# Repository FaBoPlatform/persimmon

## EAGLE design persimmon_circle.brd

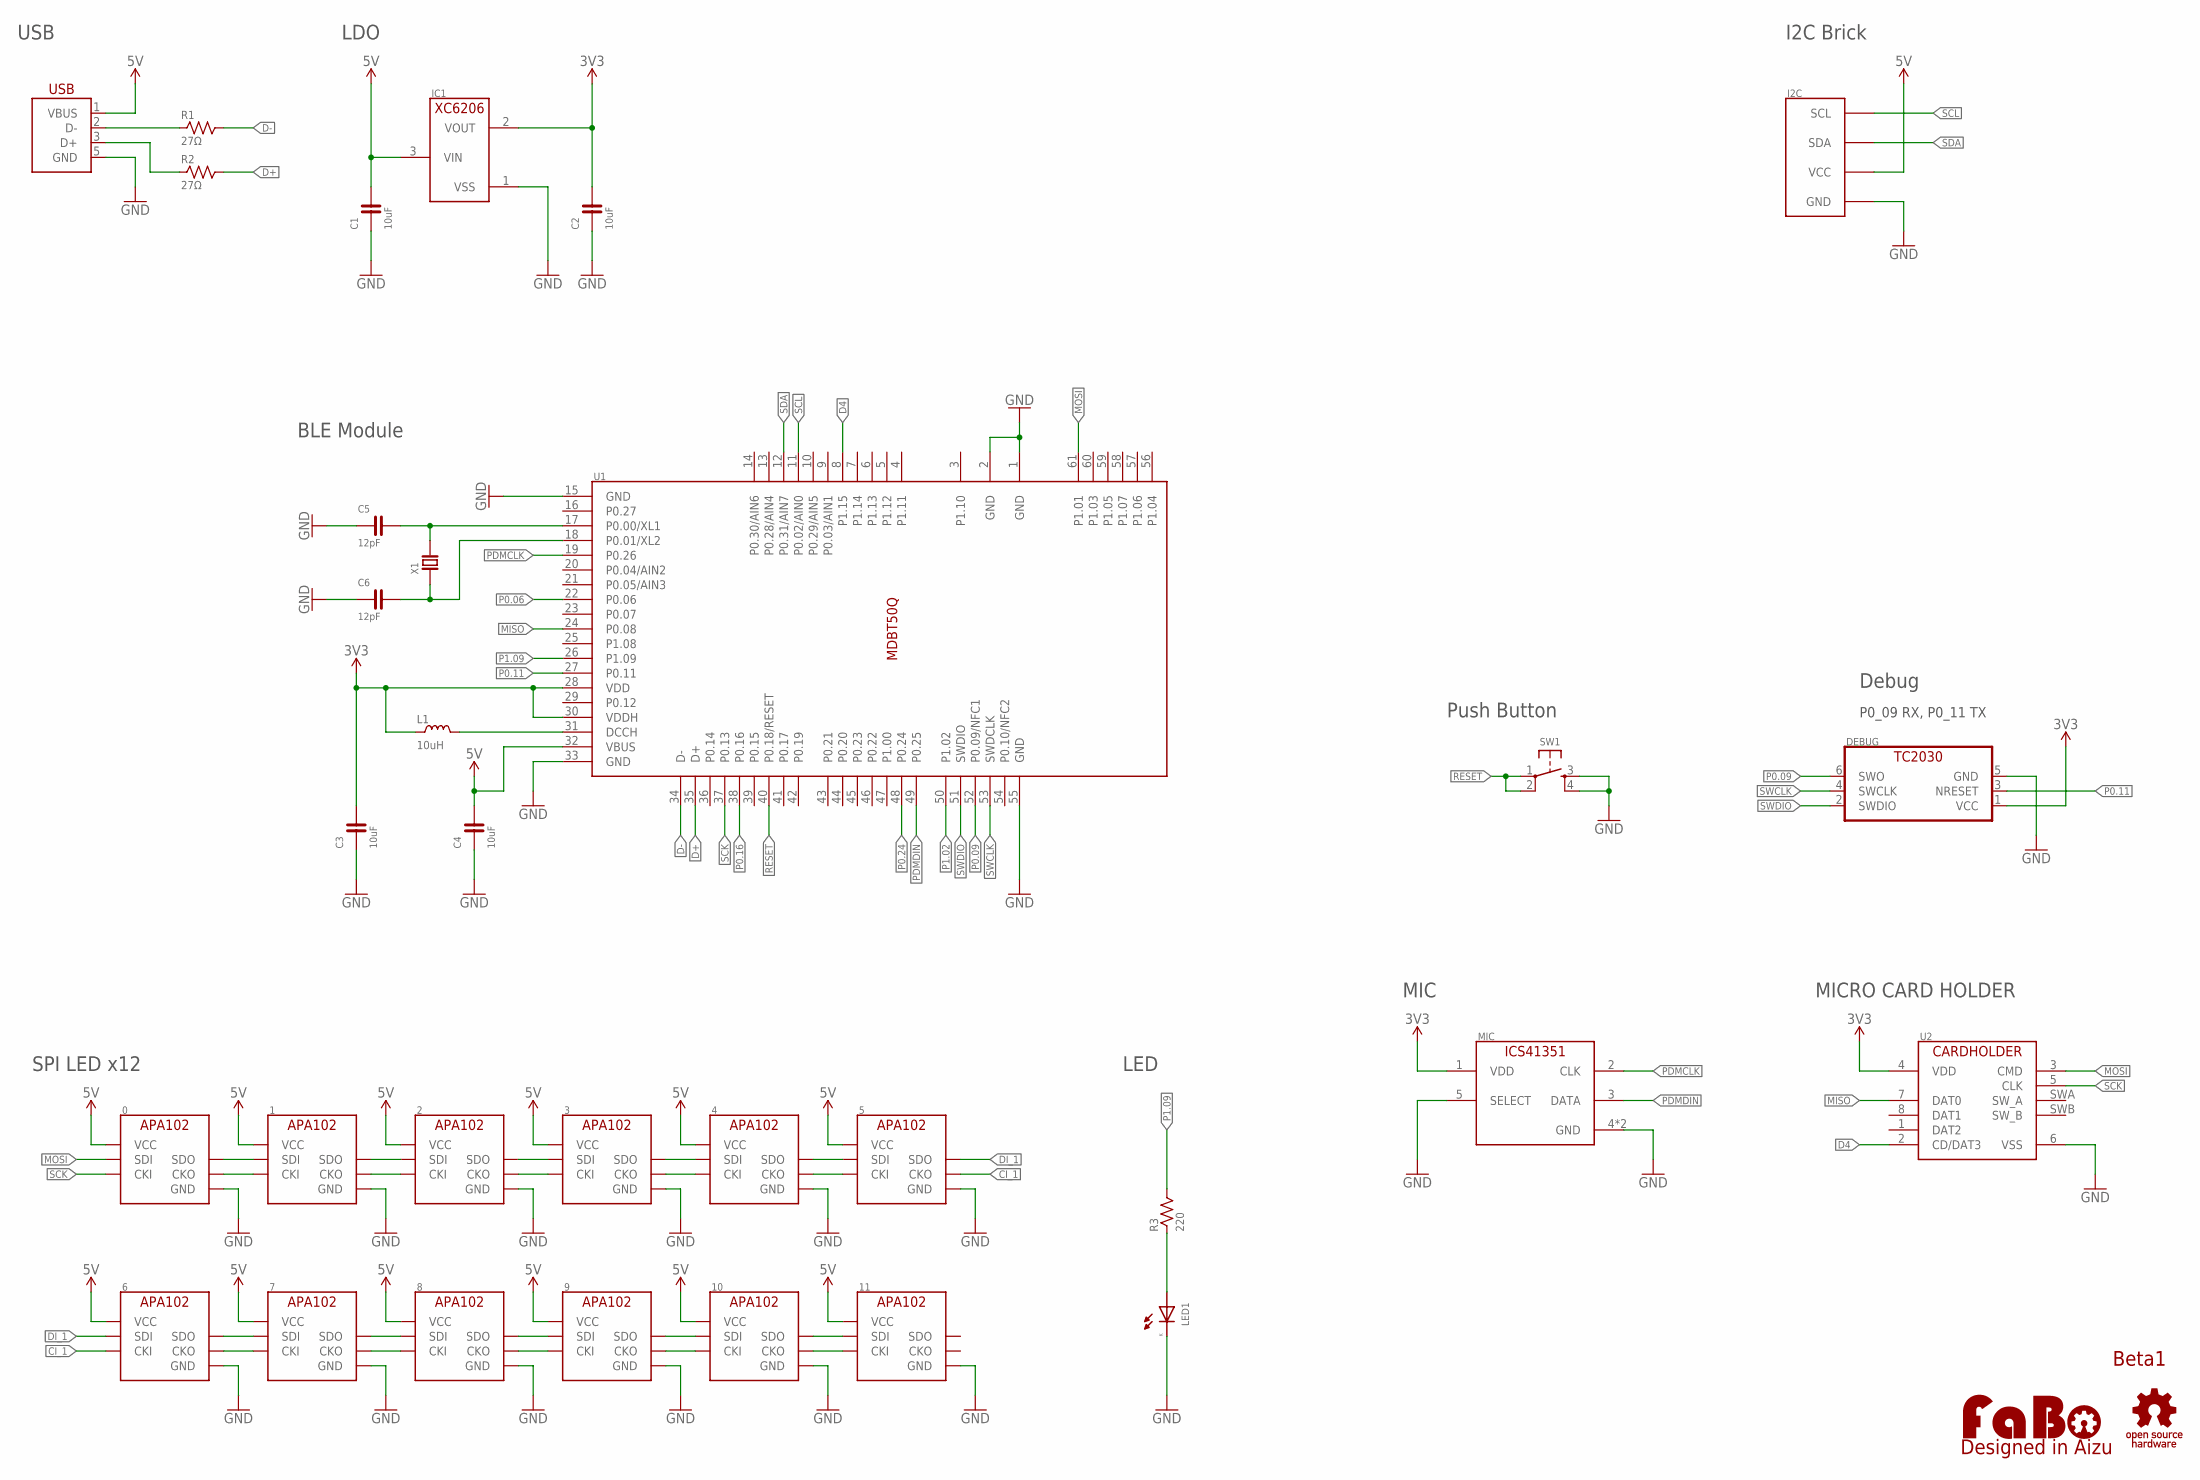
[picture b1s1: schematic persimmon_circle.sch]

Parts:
0, 1, 2, 3, 4, 5, 6, 7, 8, 9, 10, 11: APA102_IPIXEL; APA102_2020
C1, C2, C3, C4: 10uF; 0603
C5, C6: 12pF; 0603
DEBUG: TC2030-IDC-NL
I2C: FABO_BRICK_I2C-B04B-PASK-1; FABO_BRICK_I2C_B04B-PASK-1
IC1: XC6206; SOT-23
L1: 10uH; 0603
LED1: LED-0603; 0603
LOGO1: LOGO_OSHW-M_BOTTOM; LOGO_OSHW_M_BOTTOM
LOGO2: LOGO_FABO-M; LOGO_FABO_M
MIC: TDK-ICS41351; ICS41351
R1, R2: 27Ω; 0603
R3: 220; 0603
SW1: TACT-SWITCH-SMD_KMR2; KMR2
U1: MDBT50
U2: CARDHOLDER_MICRO; DM3AT-SF-PEJM5
USB: USB-ZX62D-B-5PA8; ZX62D-B-5PA8
X1: CRYSTAL-ABS07; ABRACON-ABS07-32.768KHZ

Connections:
3V3: C2.2, C3.2, DEBUG.1 (VCC), IC1.2 (VOUT), L1.1, MIC.1 (VDD), U1.28 (VDD), U1.30 (VDDH), U2.4 (VDD)
5V: 0.VCC, 1.VCC, 2.VCC, 3.VCC, 4.VCC, 5.VCC, 6.VCC, 7.VCC, 8.VCC, 9.VCC, 10.VCC, 11.VCC, C1.2, C4.2, I2C.VCC, IC1.3 (VIN), U1.32 (VBUS), USB.1 (VBUS)
CI0: 0.CKO, 1.CKI
CI1: 1.CKO, 2.CKI
CI2: 2.CKO, 3.CKI
CI3: 3.CKO, 4.CKI
CI4: 4.CKO, 5.CKI
CI6: 6.CKO, 7.CKI
CI7: 7.CKO, 8.CKI
CI8: 8.CKO, 9.CKI
CI9: 9.CKO, 10.CKI
CI10: 10.CKO, 11.CKI
CI_1: 5.CKO, 6.CKI
D4: U1.8 (P1.15), U2.2 (CD/DAT3)
D+: R2.2, U1.35 (D+)
D-: R1.2, U1.34 (D-)
DI0: 0.SDO, 1.SDI
DI1: 1.SDO, 2.SDI
DI2: 2.SDO, 3.SDI
DI3: 3.SDO, 4.SDI
DI4: 4.SDO, 5.SDI
DI6: 6.SDO, 7.SDI
DI7: 7.SDO, 8.SDI
DI8: 8.SDO, 9.SDI
DI9: 9.SDO, 10.SDI
DI10: 10.SDO, 11.SDI
DI_1: 5.SDO, 6.SDI
GND: 0.GND, 1.GND, 2.GND, 3.GND, 4.GND, 5.GND, 6.GND, 7.GND, 8.GND, 9.GND, 10.GND, 11.GND, C1.1, C2.1, C3.1, C4.1, C5.1, C6.1, DEBUG.5 (GND), I2C.GND, IC1.1 (VSS), LED1.CATHODE, MIC.4 (GND), MIC.5 (SELECT), MIC.6 (GND), SW1.3, SW1.4, U1.1 (GND), U1.2 (GND), U1.15 (GND), U1.33 (GND), U1.55 (GND), U2.6 (VSS), USB.5 (GND)
L1: L1.2, U1.31 (DCCH)
LED1: LED1.ANODE, R3.1
MISO: U1.24 (P0.08), U2.7 (DAT0)
MOSI: 0.SDI, U1.61 (P1.01), U2.3 (CMD)
P0.06: U1.22 (P0.06)
P0.09: DEBUG.6 (SWO), U1.52 (P0.09/NFC1)
P0.11: DEBUG.3 (NRESET), U1.27 (P0.11)
P0.16: U1.38 (P0.16)
P0.24: U1.48 (P0.24)
P1.02: U1.50 (P1.02)
P1.09: R3.2, U1.26 (P1.09)
PDMCLK: MIC.2 (CLK), U1.19 (P0.26)
PDMDIN: MIC.3 (DATA), U1.49 (P0.25)
RESET: SW1.1, SW1.2, U1.40 (P0.18/RESET)
SCK: 0.CKI, U1.37 (P0.13), U2.5 (CLK)
SCL: I2C.SCL, U1.11 (P0.02/AIN0)
SDA: I2C.SDA, U1.12 (P0.31/AIN7)
SWCLK: DEBUG.4 (SWCLK), U1.53 (SWDCLK)
SWDIO: DEBUG.2 (SWDIO), U1.51 (SWDIO)
USB_DM: R1.1, USB.2 (D-)
USB_DP: R2.1, USB.3 (D+)
X1: C5.2, U1.17 (P0.00/XL1), X1.P$2
X2: C6.2, U1.18 (P0.01/XL2), X1.P$1

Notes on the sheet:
Push Button
BLE Module
Debug
P0_09 RX, P0_11 TX
MIC
Beta1
USB
SPI LED x12
MICRO CARD HOLDER
I2C Brick
LED
LDO

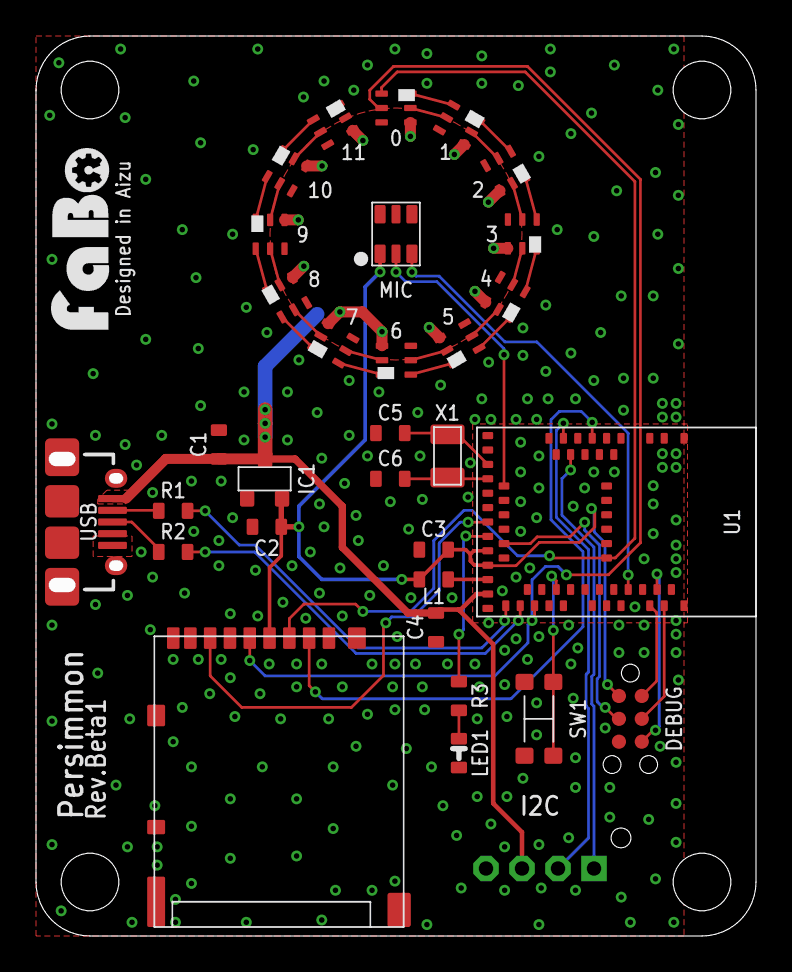
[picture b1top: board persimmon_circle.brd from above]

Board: 2 copper layers, 39.2 x 49.2 mm, 34 parts (0 on the bottom side), 47 nets.

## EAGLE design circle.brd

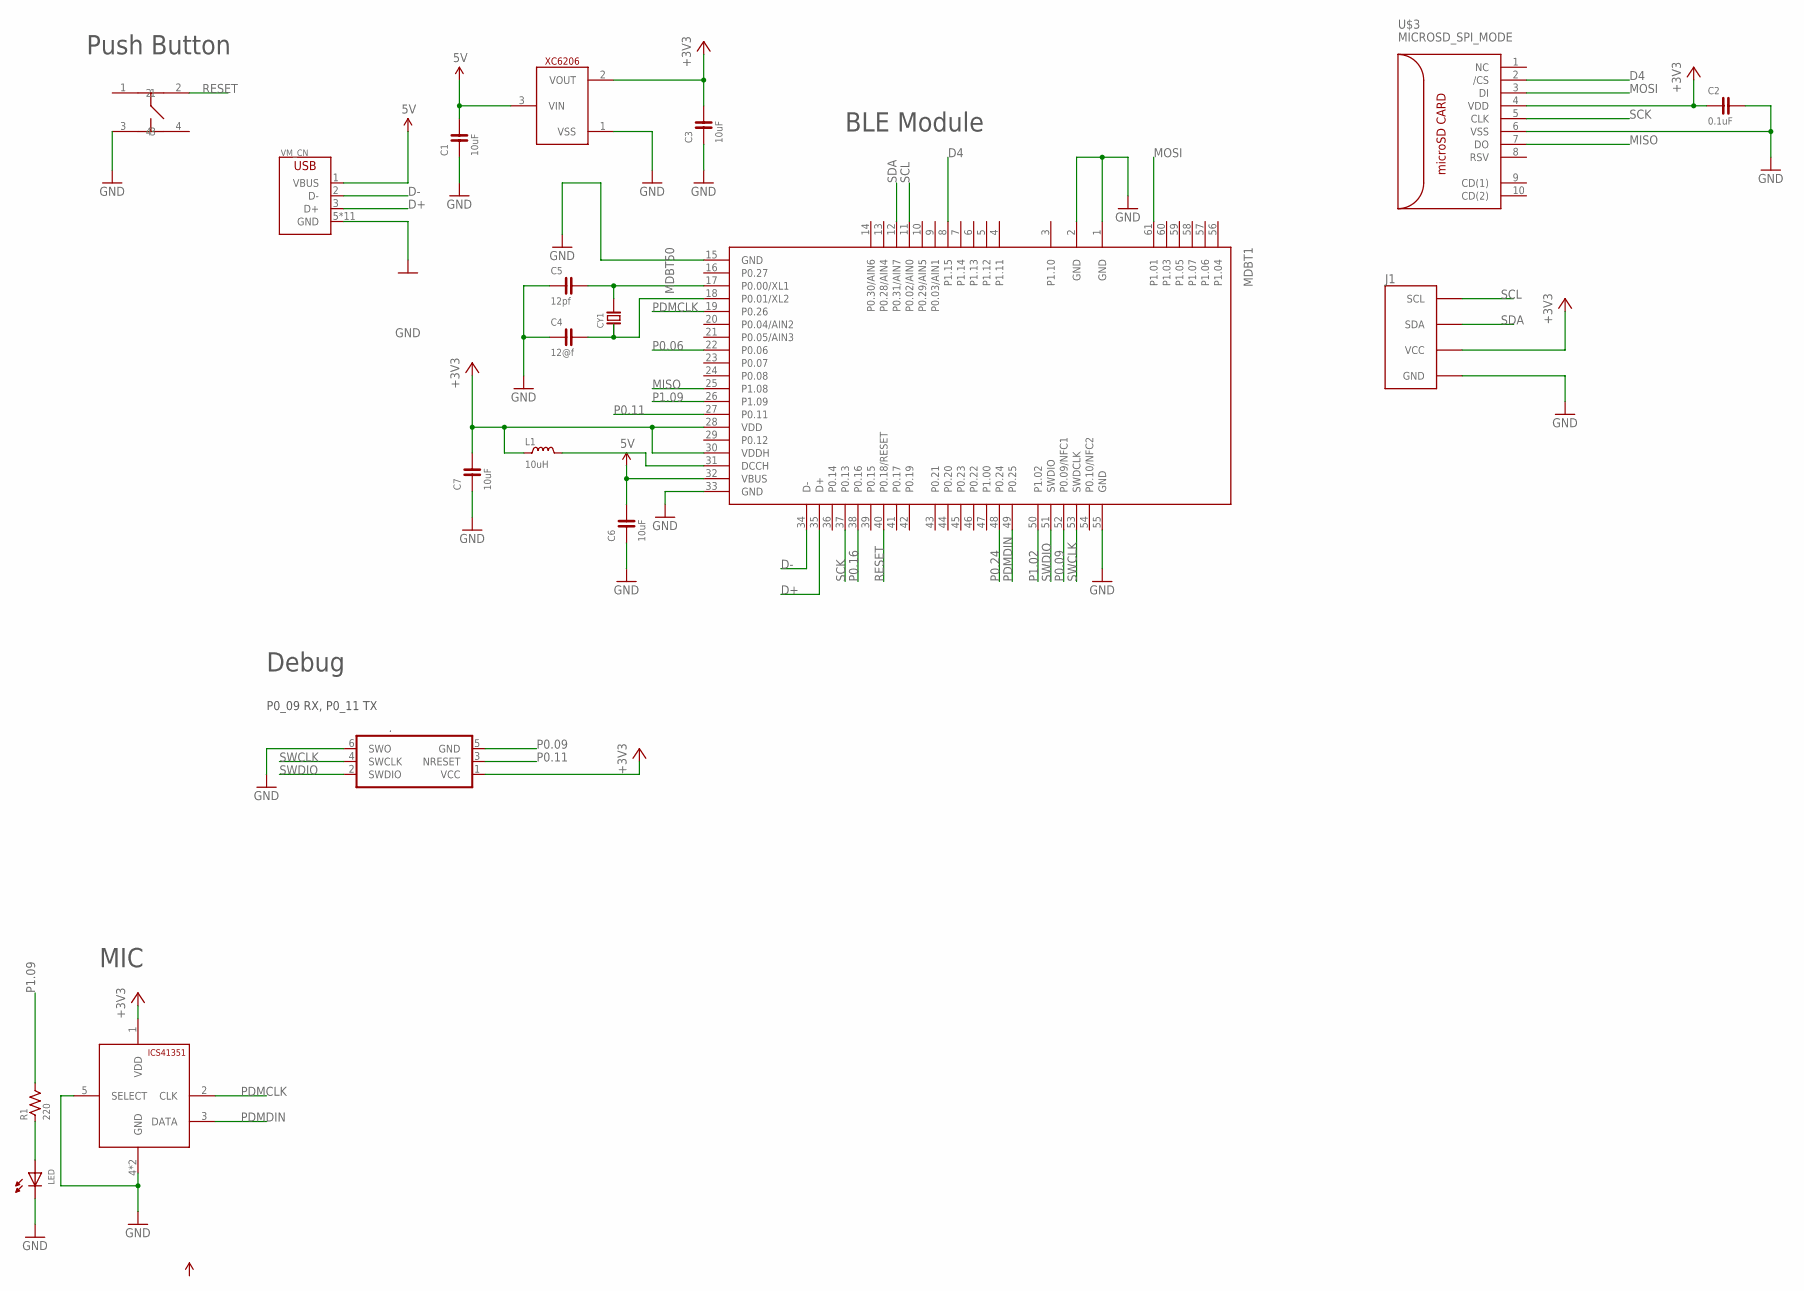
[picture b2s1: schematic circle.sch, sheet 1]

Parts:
.: TC2030-IDC-NL
C1, C3, C6, C7: 10uF; 0603
C2: 0.1uF; 0603
C4: 12@f; 0603
C5: 12pf; 0603
CY1: CRYSTAL-ABS07; ABRACON-ABS07-32.768KHZ
IC1: XC6206; SOT-23
J1: FABO_BRICK_I2C-B04B-PASK-1; FABO_BRICK_I2C_B04B-PASK-1
L1: 10uH; 0603
LED: LED-0603; 0603
MDBT1: MDBT50
MIC1: TDK-ICS41351; ICS41351
R1: 220; 0603
U$3: MICROSD_SPI_MODE; MICRO_SD_CONNECTOR
U$5: SWICTH-4P(KMR2); SWITCH-4P(KMR2)
VM_CN: USB-ZX62D; ZX62D-B-5PA8

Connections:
5V: C1.2, C6.2, IC1.3 (VIN), MDBT1.32 (VBUS), VM_CN.1 (VBUS)
+3V3: ..1 (VCC), C2.1, C3.2, C7.2, IC1.2 (VOUT), J1.VCC, L1.1, MDBT1.28 (VDD), MDBT1.30 (VDDH), MIC1.1 (VDD), U$3.4 (VDD)
D4: MDBT1.8 (P1.15), U$3.2 (/CS)
D+: MDBT1.35 (D+), VM_CN.3 (D+)
D-: MDBT1.34 (D-), VM_CN.2 (D-)
GND: ..6 (SWO), C1.1, C2.2, C3.1, C4.1, C5.1, C6.1, C7.1, IC1.1 (VSS), J1.GND, LED.CATHODE, MDBT1.1 (GND), MDBT1.2 (GND), MDBT1.15 (GND), MDBT1.33 (GND), MDBT1.55 (GND), MIC1.4 (GND), MIC1.5 (SELECT), MIC1.6 (GND), U$3.6 (VSS), U$5.3, VM_CN.5 (GND), VM_CN.B1 (GND), VM_CN.B2 (GND), VM_CN.B3 (GND), VM_CN.B4 (GND), VM_CN.T1 (GND), VM_CN.T2 (GND), VM_CN.T3 (GND), VM_CN.T4 (GND), VM_CN.T5 (GND), VM_CN.T6 (GND); also elsewhere on the board
MISO: MDBT1.25 (P1.08), U$3.7 (DO)
MOSI: MDBT1.61 (P1.01), U$3.3 (DI); also elsewhere on the board
unnamed: L1.2, MDBT1.31 (DCCH)
unnamed: LED.ANODE, R1.1
unnamed: C5.2, CY1.P$2, MDBT1.17 (P0.00/XL1)
unnamed: C4.2, CY1.P$1, MDBT1.18 (P0.01/XL2)
P0.06: MDBT1.22 (P0.06)
P0.09: ..5 (GND), MDBT1.52 (P0.09/NFC1)
P0.11: ..3 (NRESET), MDBT1.27 (P0.11)
P0.16: MDBT1.38 (P0.16)
P0.24: MDBT1.48 (P0.24)
P1.02: MDBT1.50 (P1.02)
P1.09: MDBT1.26 (P1.09), R1.2
PDMCLK: MDBT1.19 (P0.26), MIC1.2 (CLK)
PDMDIN: MDBT1.49 (P0.25), MIC1.3 (DATA)
RESET: MDBT1.40 (P0.18/RESET), U$5.2
SCK: MDBT1.37 (P0.13), U$3.5 (CLK); also elsewhere on the board
SCL: J1.SCL, MDBT1.11 (P0.02/AIN0)
SDA: J1.SDA, MDBT1.12 (P0.31/AIN7)
SWCLK: ..4 (SWCLK), MDBT1.53 (SWDCLK)
SWDIO: ..2 (SWDIO), MDBT1.51 (SWDIO)

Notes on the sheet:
Push Button
BLE Module
Debug
P0_09 RX, P0_11 TX
MIC

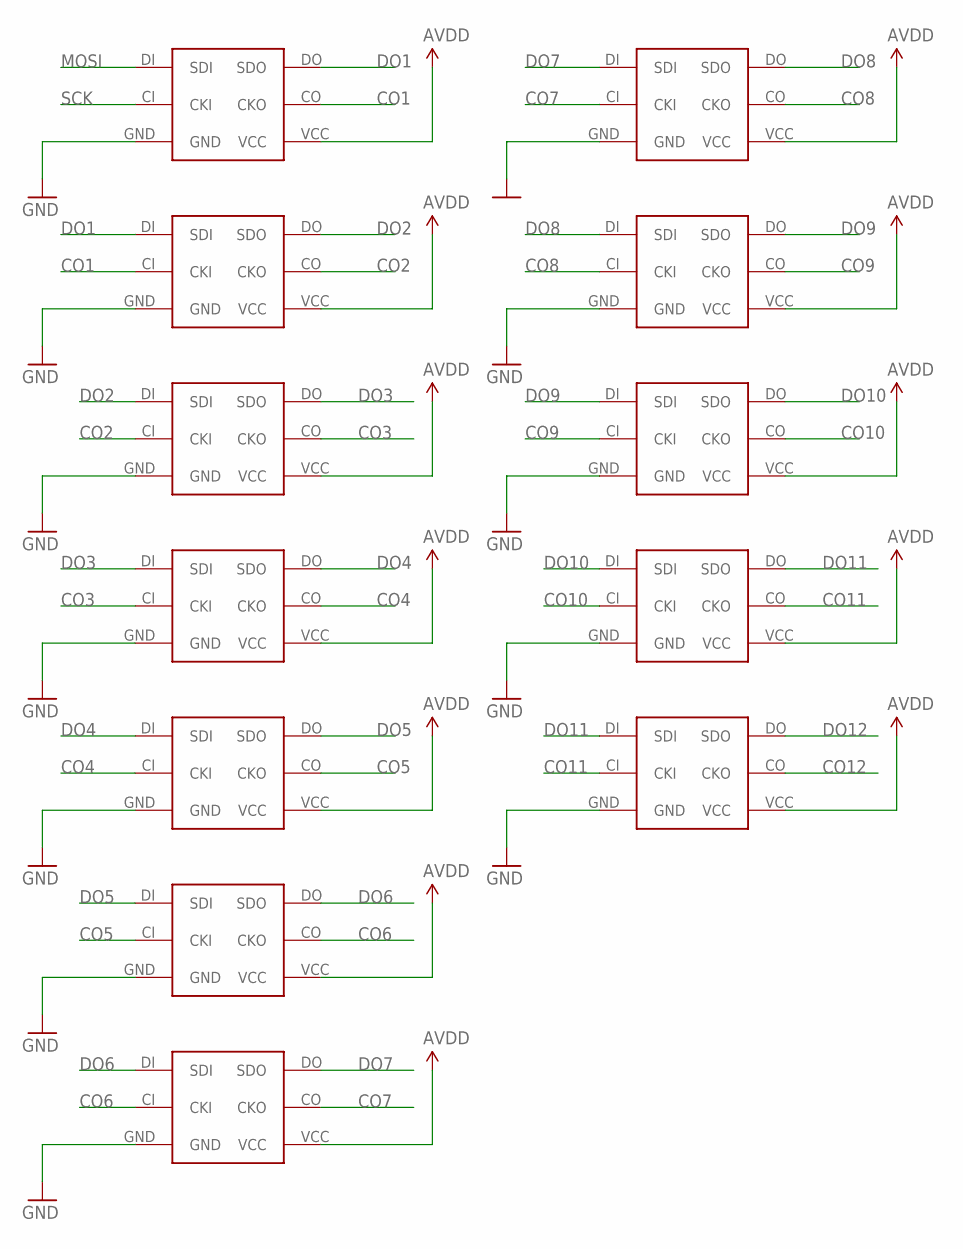
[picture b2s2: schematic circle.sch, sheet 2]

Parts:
0, 1, 2, 3, 4, 5, 6, 7, 8, 9, 10, 11: APA102_IPIXEL; APA102(IPIXEL)

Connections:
AVDD: 0.VCC, 1.VCC, 2.VCC, 3.VCC, 4.VCC, 5.VCC, 6.VCC, 7.VCC, 8.VCC, 9.VCC, 10.VCC, 11.VCC
CO1: 0.CO (CKO), 1.CI (CKI)
CO2: 1.CO (CKO), 2.CI (CKI)
CO3: 2.CO (CKO), 3.CI (CKI)
CO4: 3.CO (CKO), 4.CI (CKI)
CO5: 4.CO (CKO), 5.CI (CKI)
CO6: 5.CO (CKO), 6.CI (CKI)
CO7: 6.CO (CKO), 7.CI (CKI)
CO8: 7.CO (CKO), 8.CI (CKI)
CO9: 8.CO (CKO), 9.CI (CKI)
CO10: 9.CO (CKO), 10.CI (CKI)
CO11: 10.CO (CKO), 11.CI (CKI)
CO12: 11.CO (CKO)
DO1: 0.DO (SDO), 1.DI (SDI)
DO2: 1.DO (SDO), 2.DI (SDI)
DO3: 2.DO (SDO), 3.DI (SDI)
DO4: 3.DO (SDO), 4.DI (SDI)
DO5: 4.DO (SDO), 5.DI (SDI)
DO6: 5.DO (SDO), 6.DI (SDI)
DO7: 6.DO (SDO), 7.DI (SDI)
DO8: 7.DO (SDO), 8.DI (SDI)
DO9: 8.DO (SDO), 9.DI (SDI)
DO10: 9.DO (SDO), 10.DI (SDI)
DO11: 10.DO (SDO), 11.DI (SDI)
DO12: 11.DO (SDO)
GND: 0.GND, 1.GND, 2.GND, 3.GND, 4.GND, 5.GND, 6.GND, 7.GND, 8.GND, 9.GND, 10.GND, 11.GND; also elsewhere on the board
MOSI: 0.DI (SDI); also elsewhere on the board
SCK: 0.CI (CKI); also elsewhere on the board

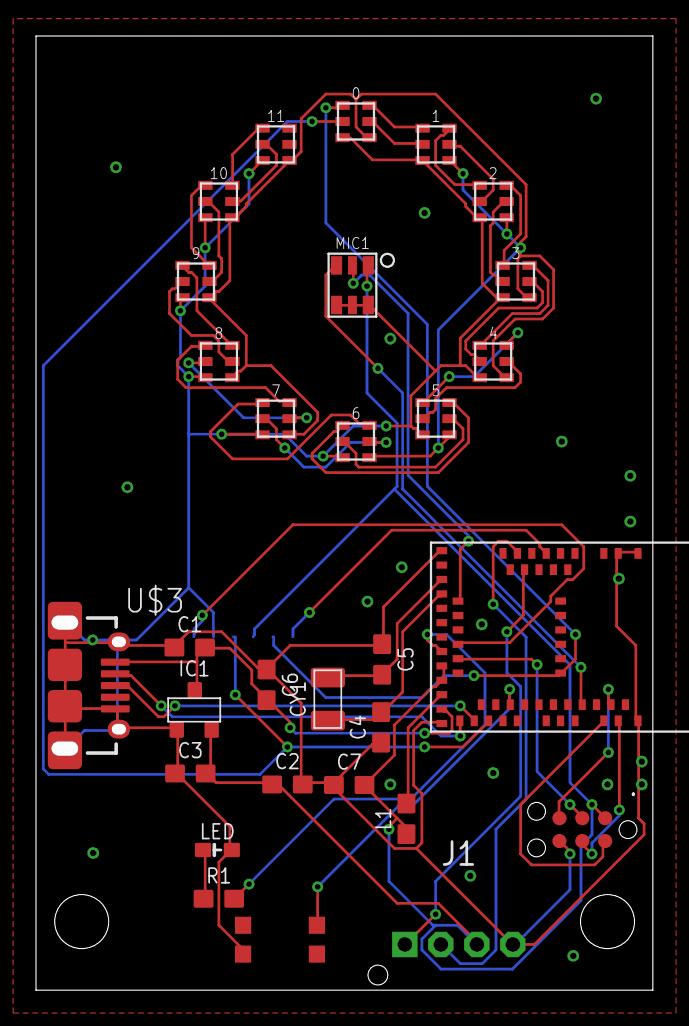
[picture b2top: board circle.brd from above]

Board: 2 copper layers, 33.5 x 52.2 mm, 31 parts (0 on the bottom side), 46 nets.

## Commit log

2021-06-23 Initial commit.
2021-06-24 (WIP)persimmon_circle 回路図修正
2021-07-01 Persimmon circle Rev.Beta1 リファイン

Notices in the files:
parts and their libraries:
FaBo-LED: Released under the Creative Commons Attribution-ShareAlike 4.0 License
https://creativecommons.org/licenses/by-sa/4.0
FaBo-Symbol: Released under the Creative Commons
SparkFun: Licensing: CC v3.0 Share-Alike You are welcome to use this library for commercial purposes.
